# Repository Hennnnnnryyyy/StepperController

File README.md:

# StepperController
A simple handheld stepper controller

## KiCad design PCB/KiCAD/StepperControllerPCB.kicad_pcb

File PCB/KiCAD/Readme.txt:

Attempting to migrate everything to KiCad

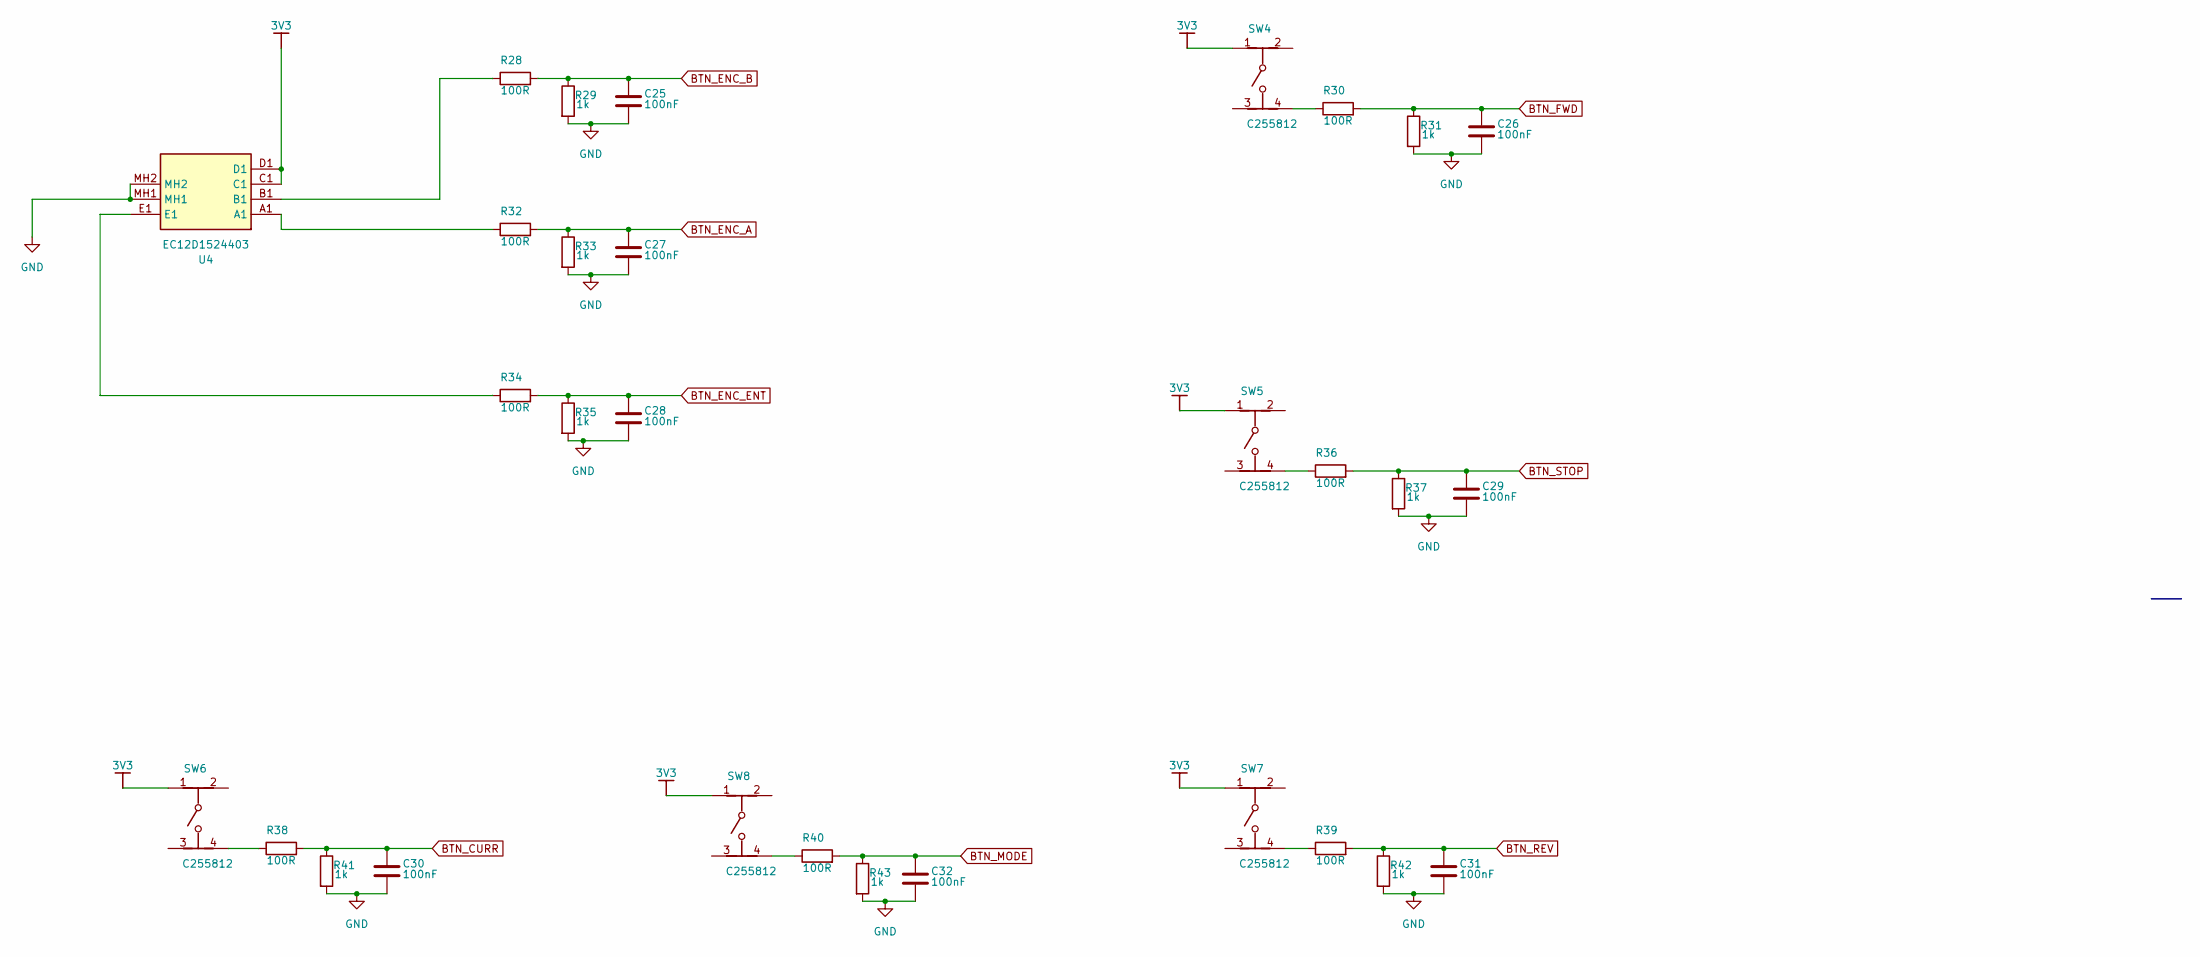
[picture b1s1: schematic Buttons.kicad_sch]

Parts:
C25, C26, C27, C28, C29, C30, C31, C32: 100nF; C_0603_1608Metric
R28, R30, R32, R34, R36, R38, R39, R40: 100R; R_0603_1608Metric
R29, R31, R33, R35, R37, R41, R42, R43: 1k; R_0603_1608Metric
SW4, SW5, SW6, SW7, SW8: C255812; FSM2J_1; VOLTAGE RATING DC 24V; MANUFACTURER PART NUMBER FSM2JSMAA; MOUSER DESCRIPTION Tactile Switches TACTILE 260G FORCE S
U4: EC12D1524403; Mouser Part Number 688-EC12D1524403

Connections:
3V3: SW4.1, SW5.1, SW6.1, SW7.1, SW8.1, U4.C1, U4.D1; also elsewhere on the board
BTN_CURR: C30.1, R38.2, R41.1; also elsewhere on the board
BTN_ENC_A: C27.1, R32.2, R33.1; also elsewhere on the board
BTN_ENC_B: C25.1, R28.2, R29.1; also elsewhere on the board
BTN_ENC_ENT: C28.1, R34.2, R35.1; also elsewhere on the board
BTN_FWD: C26.1, R30.2, R31.1; also elsewhere on the board
BTN_MODE: C32.1, R40.2, R43.1; also elsewhere on the board
BTN_REV: C31.1, R39.2, R42.1; also elsewhere on the board
BTN_STOP: C29.1, R36.2, R37.1; also elsewhere on the board
GND: C25.2, C26.2, C27.2, C28.2, C29.2, C30.2, C31.2, C32.2, R29.2, R31.2, R33.2, R35.2, R37.2, R41.2, R42.2, R43.2, U4.MH1, U4.MH2; also elsewhere on the board
unnamed: R28.1, U4.B1
unnamed: R30.1, SW4.4
unnamed: R32.1, U4.A1
unnamed: R34.1, U4.E1
unnamed: R36.1, SW5.4
unnamed: R38.1, SW6.4
unnamed: R39.1, SW7.4
unnamed: R40.1, SW8.4

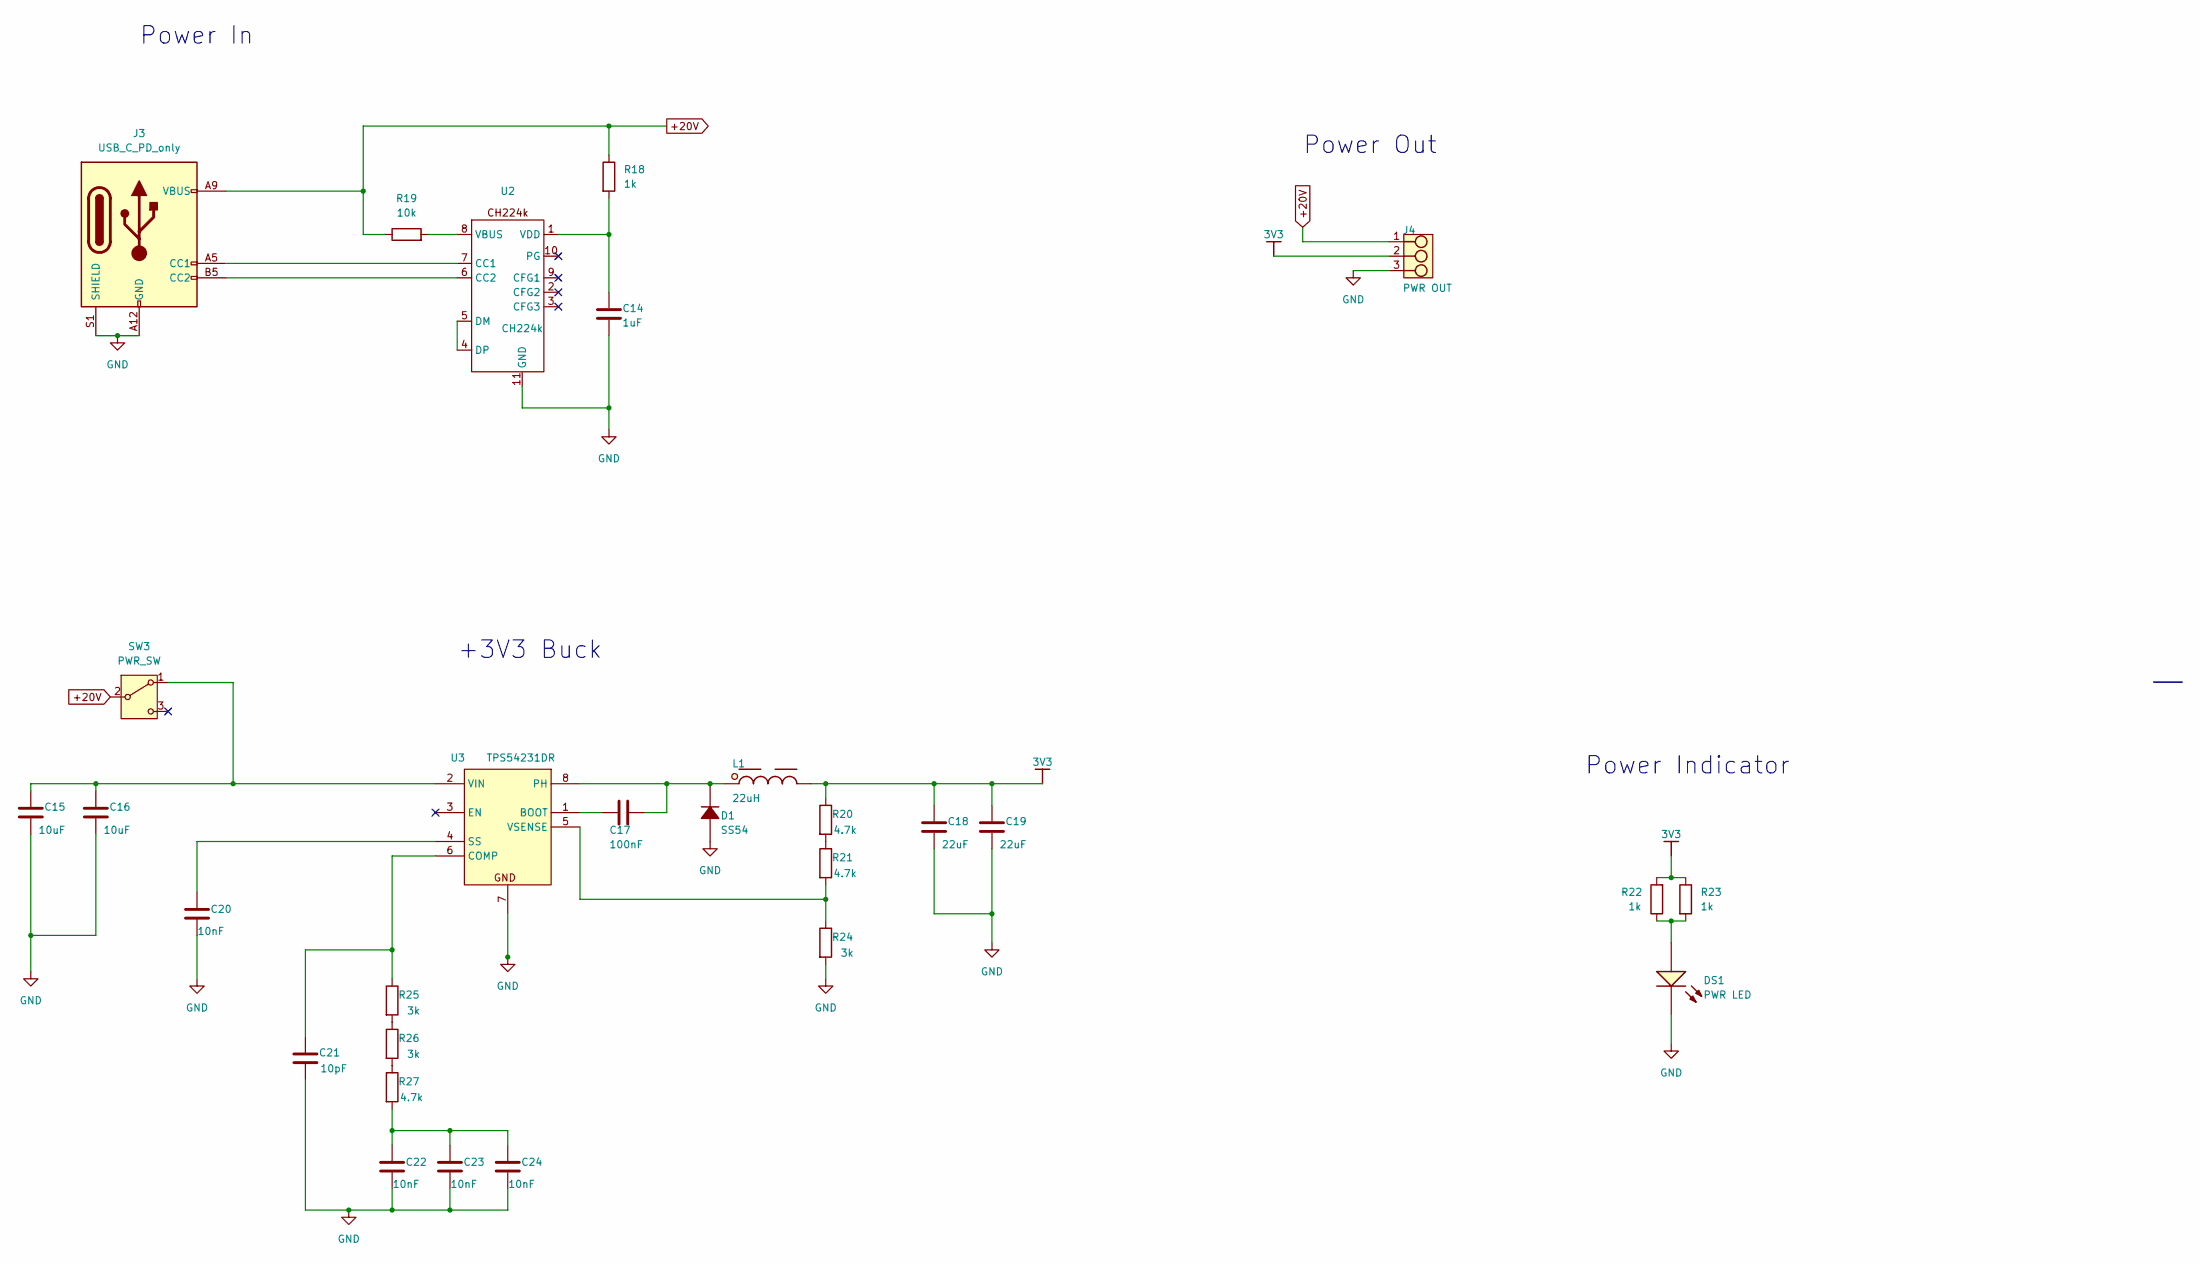
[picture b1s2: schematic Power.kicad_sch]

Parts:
C14: 1uF; C_0603_1608Metric; TOLERANCE ±20%; VOLTAGE - RATED 25V; PART NUMBER 250X14W223MV4T
C15, C16: 10uF; C_1206_3216Metric
C17: 100nF; C_0603_1608Metric
C18, C19: 22uF; C_1206_3216Metric
C20, C22, C23, C24: 10nF; C_0603_1608Metric
C21: 10pF; C_0603_1608Metric
D1: SS54; D_SMA; VOLTAGE - DC REVERSE (V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 50V; VOLTAGE - FORWARD (VF) 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 1.3V @ 1A; PART NUMBER SS54; LCSC C22452
DS1: PWR LED; LED_1206_3216Metric; FORWARD VOLTAGE 1.8V; LCSC C84270
J3: USB_C_PD_only; USB_C_Receptacle_GCT_USB4125-xx-x_6P_TopMnt_Horizontal; LCSC C18357551
J4: PWR OUT; TerminalBlock_RND_205-00288_1x03_P5.08mm_Horizontal; PARTNUMBER 1760500000; LCSC C430602
L1: 22uH; SMDRH105R; INDUCTANCE TOLERANCE 20%; TOLERANCE 20%; LCSC C10165
R18, R22, R23: 1k; R_0603_1608Metric
R19: 10k; R_0603_1608Metric
R20, R21, R27: 4.7k; R_0603_1608Metric
R24, R25, R26: 3k; R_0603_1608Metric
SW3: PWR_SW; Swtich SS-12F44-G5; LCSC C136718
U2: CH224k; SSOP-10_3.9x4.9mm_P1.00mm; LCSC C970725
U3: TPS54231DR; SOIC-8_3.9x4.9mm_P1.27mm; RATING Catalog; PARTNUMBER TPS54231DR; LCSC C28023

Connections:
3V3: C18.1, C19.1, J4.2 (A2), L1.2, R20.1, R22.2, R23.1; also elsewhere on the board
+20V: J3.A9 (VBUS), J3.B9 (VBUS), J4.1 (A1), R18.1, R19.1, SW3.2 (B); also elsewhere on the board
GND: C14.2, C15.2, C16.2, C18.2, C19.2, C20.2, C21.2, C22.2, C23.2, C24.2, D1.1, DS1.2 (K), J3.A12 (GND), J3.B12 (GND), J3.S1 (SHIELD), J4.3 (A3), R24.2, U2.11 (GND), U3.7 (GND); also elsewhere on the board
unnamed: C22.1, C23.1, C24.1, R27.2
unnamed: DS1.1 (A), R22.1, R23.2
unnamed: J3.A5 (CC1), U2.7 (CC1)
unnamed: J3.B5 (CC2), U2.6 (CC2)
unnamed: R20.2, R21.1
unnamed: R25.2, R26.1
unnamed: R26.2, R27.1
unnamed: C15.1, C16.1, SW3.1 (A), U3.2 (VIN)
unnamed: U2.4 (DP), U2.5 (DM)
unnamed: R19.2, U2.8 (VBUS)
unnamed: C14.1, R18.2, U2.1 (VDD)
unnamed: C17.2, U3.1 (BOOT)
unnamed: C21.1, R25.1, U3.6 (COMP)
unnamed: C17.1, D1.2, L1.1, U3.8 (PH)
unnamed: C20.1, U3.4 (SS)
unnamed: R21.2, R24.1, U3.5 (VSENSE)

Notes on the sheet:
Power Out
Power In
+3V3 Buck
Power Indicator

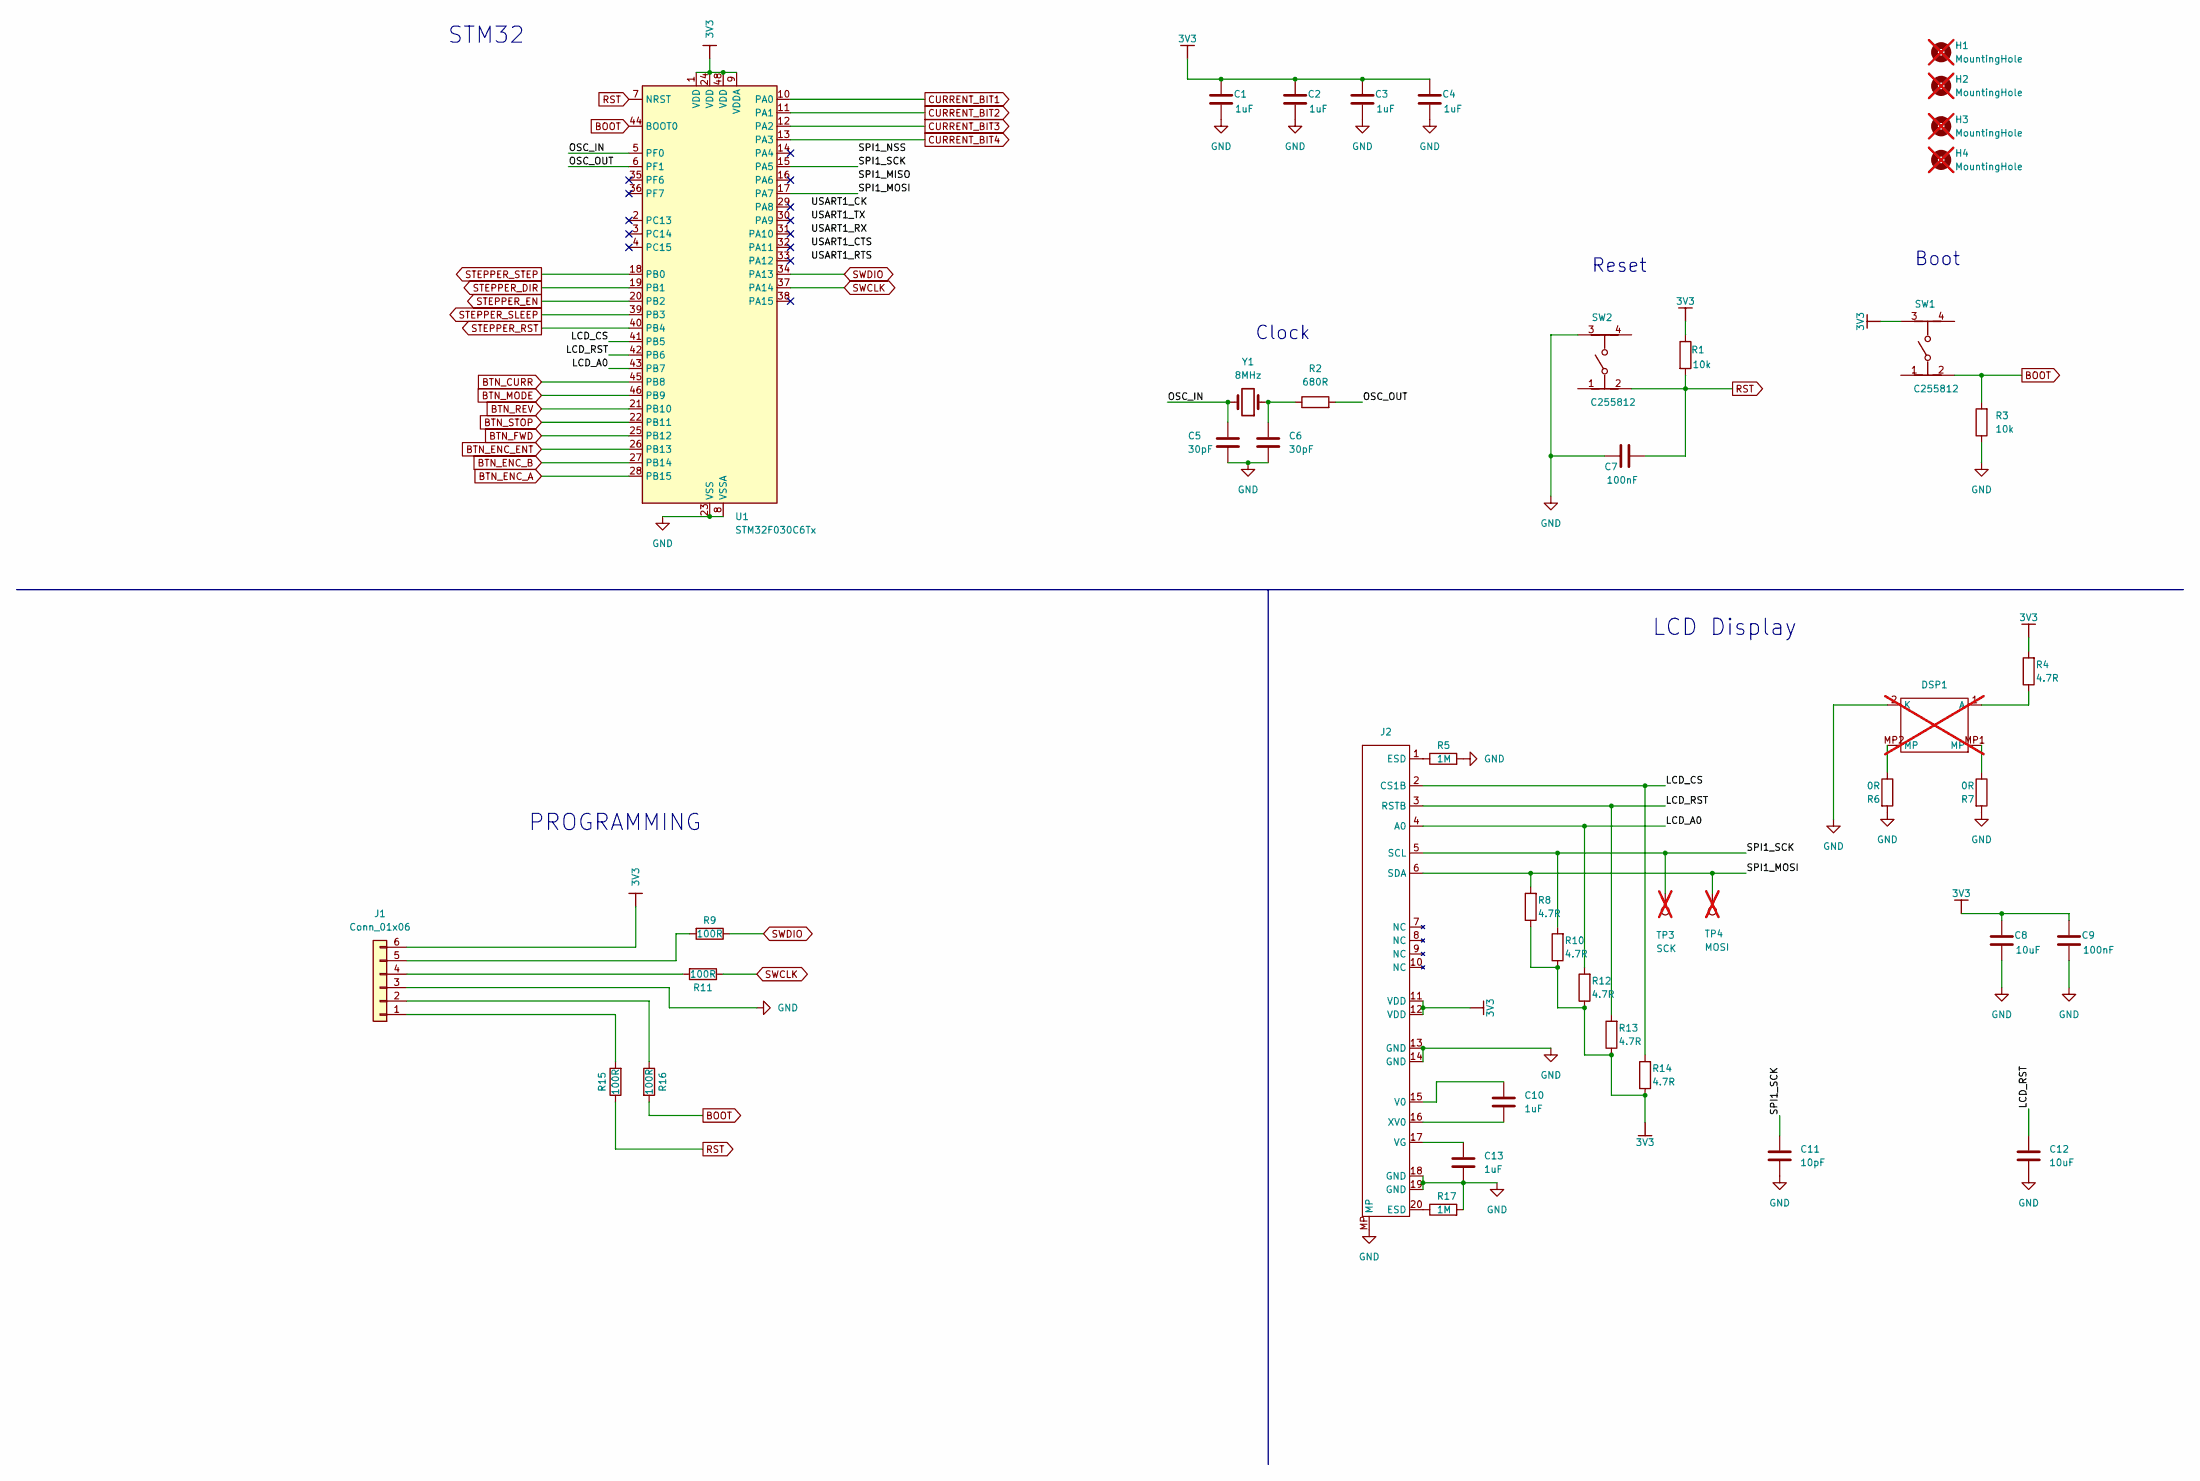
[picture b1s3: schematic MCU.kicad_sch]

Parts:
C1, C2, C3, C4, C10, C13: 1uF; C_0603_1608Metric
C5, C6: 30pF; C_0603_1608Metric
C7, C9: 100nF; C_0603_1608Metric
C8, C12: 10uF; C_1206_3216Metric
C11: 10pF; C_0603_1608Metric
DSP1: HS12864G19C Display; not fitted
H1, H2, H3, H4: MountingHole; MountingHole_3.2mm_M3; not fitted
J1: Conn_01x06; PinHeader_1x06_P2.54mm_Vertical; LCSC C37208
J2: AFC01-S20FFC-00; LCSC C262274
R1, R3: 10k; R_0603_1608Metric
R2: 680R; R_0603_1608Metric
R4, R8, R10, R12, R13, R14: 4.7R; R_0603_1608Metric
R5, R17: 1M; R_0603_1608Metric
R6, R7: 0R; R_0603_1608Metric
R9, R11, R15, R16: 100R; R_0603_1608Metric
SW1, SW2: C255812; FSM2J_1; VOLTAGE RATING DC 24V; MANUFACTURER PART NUMBER FSM2JSMAA; MOUSER DESCRIPTION Tactile Switches TACTILE 260G FORCE S
TP3: SCK; TestPoint_Pad_D2.0mm; not fitted
TP4: MOSI; TestPoint_Pad_D2.0mm; not fitted
U1: STM32F030C6Tx; LQFP-48_7x7mm_P0.5mm; LCSC C62514
Y1: 8MHz; Crystal_SMD_HC49-SD; LCSC C12674

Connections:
3V3: C1.1, C2.1, C3.1, C4.1, C8.1, C9.1, J1.6, J2.11 (VDD), J2.12 (VDD), R1.1, R4.2, R8.1, R10.1, R12.1, R13.1, R14.1, SW1.3, U1.1 (VDD), U1.9 (VDDA), U1.24 (VDD), U1.48 (VDD); also elsewhere on the board
/MCU/LCD_A0: J2.4 (A0), R12.2, U1.43 (PB7)
/MCU/LCD_CS: J2.2 (CS1B), R14.2, U1.41 (PB5)
/MCU/LCD_RST: C12.1, J2.3 (RSTB), R13.2, U1.42 (PB6)
/MCU/OSC_IN: C5.2, U1.5 (PF0), Y1.2
/MCU/OSC_OUT: R2.2, U1.6 (PF1)
/MCU/SPI1_MOSI: J2.6 (SDA), R8.2, TP4.1, U1.17 (PA7)
/MCU/SPI1_SCK: C11.1, J2.5 (SCL), R10.2, TP3.1, U1.15 (PA5)
BOOT: R3.2, R16.2, SW1.2, U1.44 (BOOT0)
BTN_CURR: U1.45 (PB8); also elsewhere on the board
BTN_ENC_A: U1.28 (PB15); also elsewhere on the board
BTN_ENC_B: U1.27 (PB14); also elsewhere on the board
BTN_ENC_ENT: U1.26 (PB13); also elsewhere on the board
BTN_FWD: U1.25 (PB12); also elsewhere on the board
BTN_MODE: U1.46 (PB9); also elsewhere on the board
BTN_REV: U1.21 (PB10); also elsewhere on the board
BTN_STOP: U1.22 (PB11); also elsewhere on the board
CURRENT_BIT1: U1.10 (PA0); also elsewhere on the board
CURRENT_BIT2: U1.11 (PA1); also elsewhere on the board
CURRENT_BIT3: U1.12 (PA2); also elsewhere on the board
CURRENT_BIT4: U1.13 (PA3); also elsewhere on the board
GND: C1.2, C2.2, C3.2, C4.2, C5.1, C6.1, C7.1, C8.2, C9.2, C11.2, C12.2, C13.2, DSP1.2 (K), J1.3, J2.13 (GND), J2.14 (GND), J2.18 (GND), J2.19 (GND), J2.MP, R3.1, R5.2, R6.2, R7.2, R17.2, SW2.3, U1.8 (VSSA), U1.23 (VSS), U1.47 (VSS); also elsewhere on the board
unnamed: C6.2, R2.1, Y1.1
unnamed: DSP1.1 (A), R4.1
unnamed: DSP1.MP1 (MP), R7.1
unnamed: DSP1.MP2 (MP), R6.1
unnamed: J1.1, R15.2
unnamed: J1.2, R16.1
unnamed: J1.4, R11.2
unnamed: J1.5, R9.2
unnamed: J2.1 (ESD), R5.1
unnamed: J2.20 (ESD), R17.1
unnamed: C10.1, J2.15 (V0)
unnamed: C13.1, J2.17 (VG)
unnamed: C10.2, J2.16 (XV0)
RST: C7.2, R1.2, R15.1, SW2.2, U1.7 (NRST)
STEPPER_DIR: U1.19 (PB1); also elsewhere on the board
STEPPER_EN: U1.20 (PB2); also elsewhere on the board
STEPPER_RST: U1.40 (PB4); also elsewhere on the board
STEPPER_SLEEP: U1.39 (PB3); also elsewhere on the board
STEPPER_STEP: U1.18 (PB0); also elsewhere on the board
SWCLK: R11.1, U1.37 (PA14)
SWDIO: R9.1, U1.34 (PA13)

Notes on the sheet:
Reset
Clock
Boot
LCD Display
STM32
PROGRAMMING

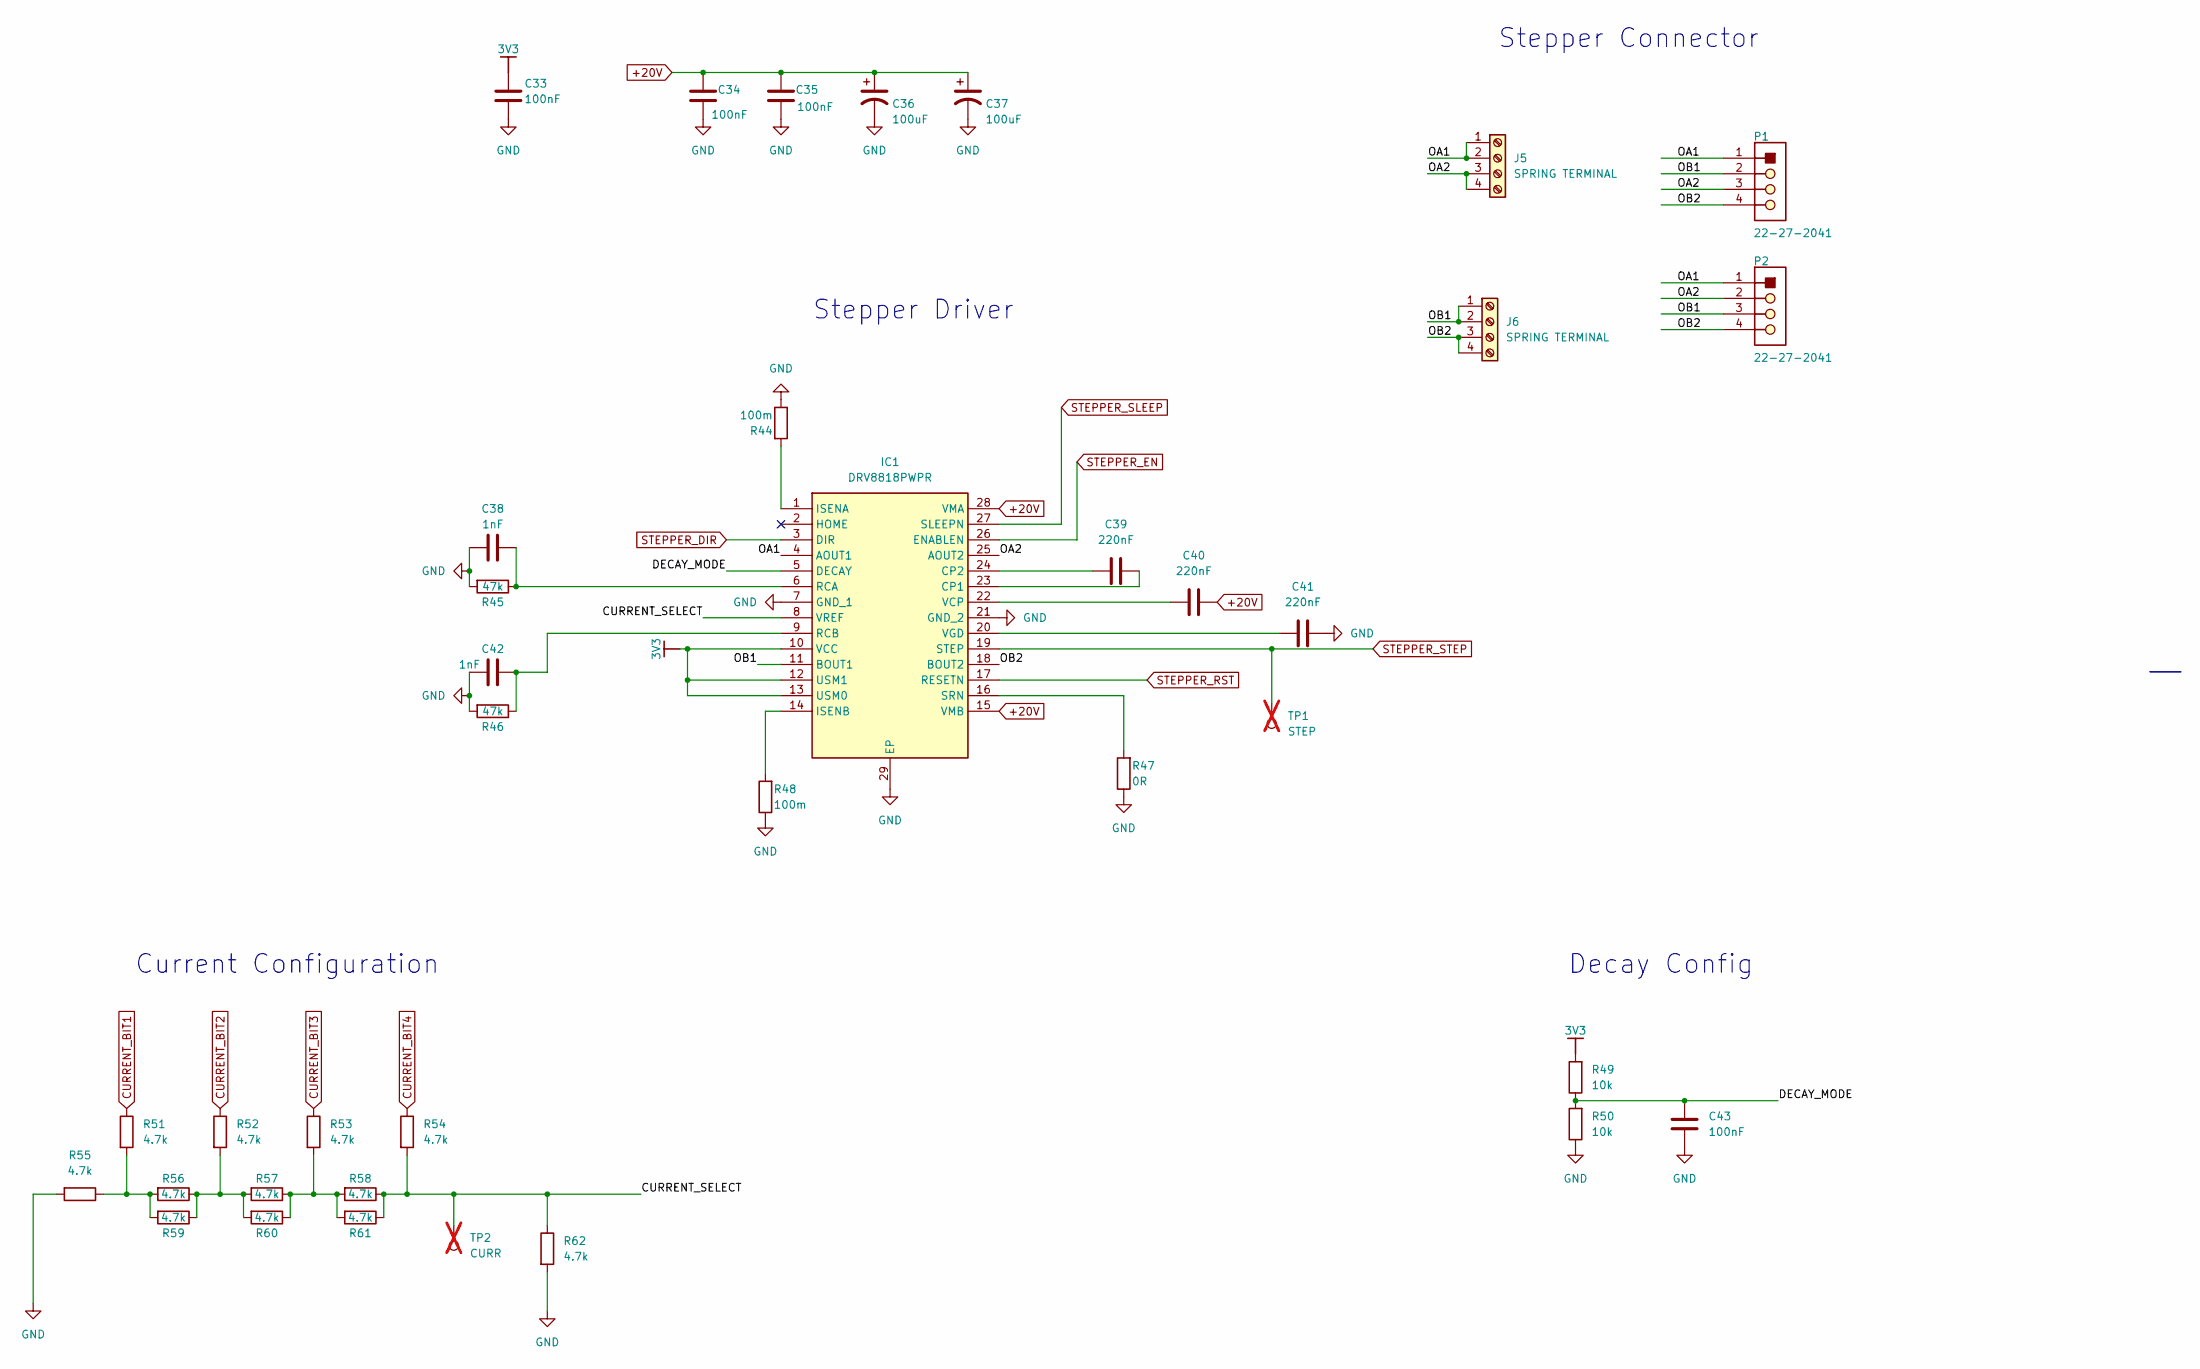
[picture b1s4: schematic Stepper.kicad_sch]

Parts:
C33, C34, C35, C43: 100nF; C_0603_1608Metric
C36, C37: 100uF; CP_Elec_8x10; LCSC C176665
C38, C42: 1nF; C_0603_1608Metric
C39, C40, C41: 220nF; C_0603_1608Metric
IC1: DRV8818PWPR; SOP65P640X120-29N; Mouser Part Number 595-DRV8818PWPR
J5, J6: SPRING TERMINAL; MX235-5.0-04P; LCSC C5349564
P1, P2: 22-27-2041; Molex_KK-254_AE-6410-04A_1x04_P2.54mm_Vertical; VOLTAGE RATING 250V; CURRENT RATING 4A; LCSC C239364
R44, R48: 100m; R_1206_3216Metric
R45, R46: 47k; R_0603_1608Metric
R47: 0R; R_0603_1608Metric
R49, R50: 10k; R_0603_1608Metric
R51, R52, R53, R54, R55, R56, R57, R58, R59, R60, R61, R62: 4.7k; R_0603_1608Metric
TP1: STEP; TestPoint_Pad_D2.0mm; not fitted
TP2: CURR; TestPoint_Pad_D2.0mm; not fitted

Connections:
3V3: C33.1, IC1.10 (VCC), IC1.12 (USM1), IC1.13 (USM0), R49.2; also elsewhere on the board
+20V: C34.1, C35.1, C36.1, C37.1, C40.2, IC1.15 (VMB), IC1.28 (VMA); also elsewhere on the board
/Stepper/CURRENT_SELECT: IC1.8 (VREF), R54.2, R58.1, R61.1, R62.1, TP2.1
/Stepper/DECAY_MODE: C43.1, IC1.5 (DECAY), R49.1, R50.2
/Stepper/OA1: IC1.4 (AOUT1), J5.1, J5.2, P1.1, P2.1
/Stepper/OA2: IC1.25 (AOUT2), J5.3, J5.4, P1.3, P2.2
/Stepper/OB1: IC1.11 (BOUT1), J6.1, J6.2, P1.2, P2.3
/Stepper/OB2: IC1.18 (BOUT2), J6.3, J6.4, P1.4, P2.4
CURRENT_BIT1: R51.1; also elsewhere on the board
CURRENT_BIT2: R52.1; also elsewhere on the board
CURRENT_BIT3: R53.1; also elsewhere on the board
CURRENT_BIT4: R54.1; also elsewhere on the board
GND: C33.2, C34.2, C35.2, C36.2, C37.2, C38.1, C41.2, C42.1, C43.2, IC1.7 (GND_1), IC1.21 (GND_2), IC1.29 (EP), R44.1, R45.2, R46.2, R47.1, R48.1, R50.1, R55.2, R62.2; also elsewhere on the board
unnamed: C39.2, IC1.23 (CP1)
unnamed: C39.1, IC1.24 (CP2)
unnamed: IC1.1 (ISENA), R44.2
unnamed: IC1.14 (ISENB), R48.2
unnamed: C38.2, IC1.6 (RCA), R45.1
unnamed: C42.2, IC1.9 (RCB), R46.1
unnamed: IC1.16 (SRN), R47.2
unnamed: C40.1, IC1.22 (VCP)
unnamed: C41.1, IC1.20 (VGD)
unnamed: R51.2, R55.1, R56.2, R59.2
unnamed: R52.2, R56.1, R57.2, R59.1, R60.2
unnamed: R53.2, R57.1, R58.2, R60.1, R61.2
STEPPER_DIR: IC1.3 (DIR); also elsewhere on the board
STEPPER_EN: IC1.26 (ENABLEN); also elsewhere on the board
STEPPER_RST: IC1.17 (RESETN); also elsewhere on the board
STEPPER_SLEEP: IC1.27 (SLEEPN); also elsewhere on the board
STEPPER_STEP: IC1.19 (STEP), TP1.1; also elsewhere on the board

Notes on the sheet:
Current Configuration
Stepper Connector
Stepper Driver
Decay Config

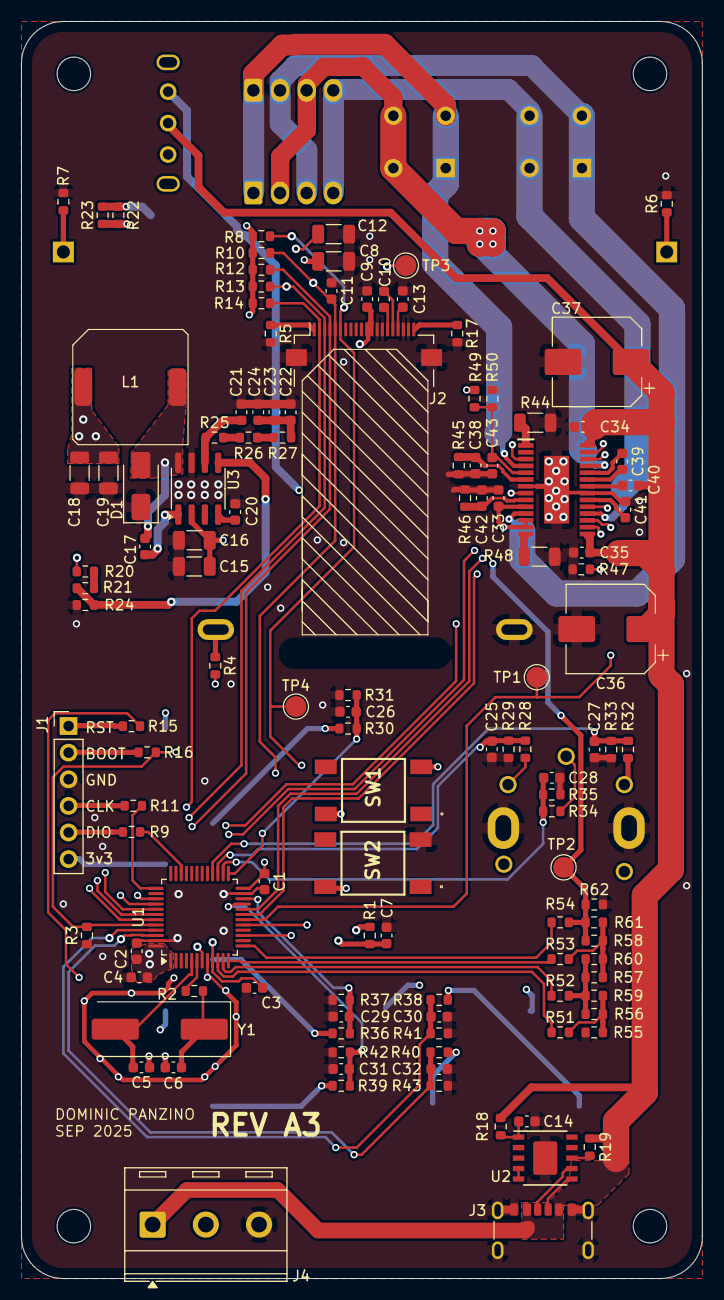
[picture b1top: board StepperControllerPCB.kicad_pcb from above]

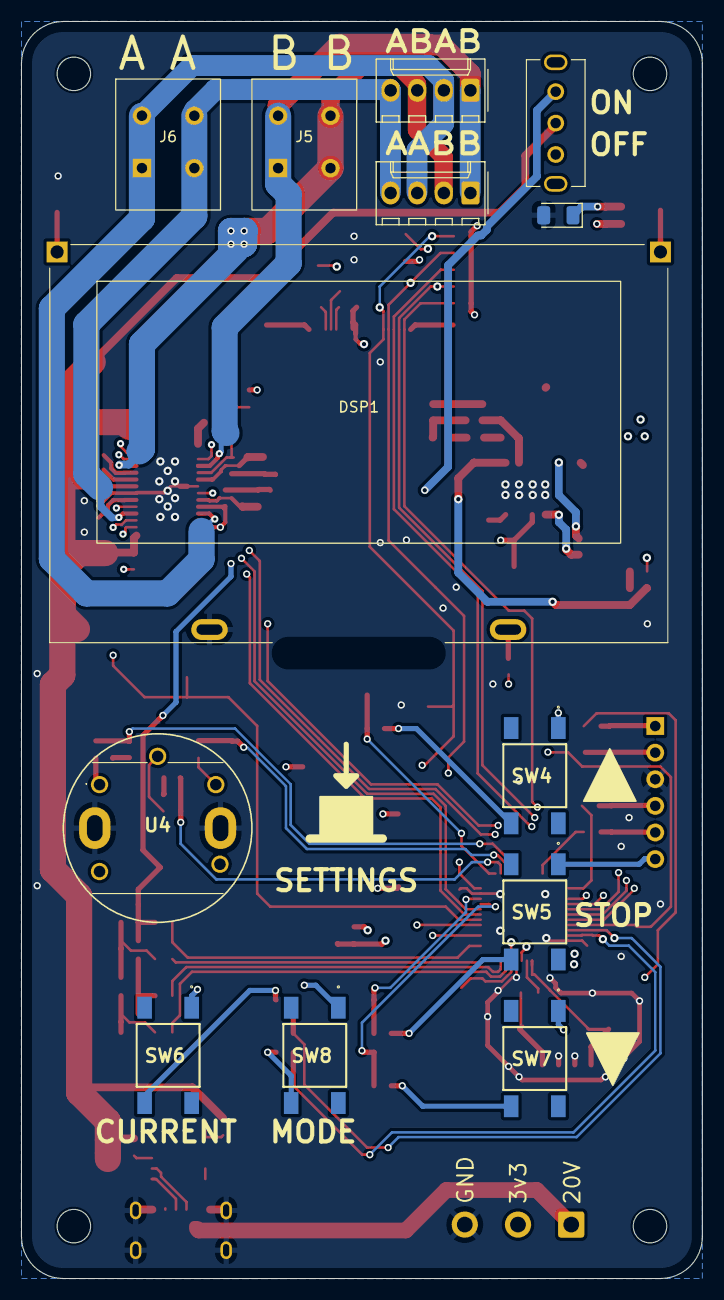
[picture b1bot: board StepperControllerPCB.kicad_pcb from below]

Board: 4 copper layers, 65.0 x 120.0 mm, 139 parts (13 on the bottom side), 86 nets.

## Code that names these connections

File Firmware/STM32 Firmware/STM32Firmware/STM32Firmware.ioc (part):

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Mcu.Name=STM32F030C6Tx
Mcu.Package=LQFP48
Mcu.UserName=STM32F030C6Tx
PA0.GPIOParameters=GPIO_Label
PA0.GPIO_Label=CurrentBit1
PA0.Signal=GPIO_Output
PA1.GPIOParameters=GPIO_Label
PA1.GPIO_Label=CurrentBit2
PA1.Signal=GPIO_Output
PA13.Mode=Serial_Wire
PA13.Signal=SYS_SWDIO
PA14.Mode=Serial_Wire
PA14.Signal=SYS_SWCLK
PA2.GPIOParameters=GPIO_Label
PA2.GPIO_Label=CurrentBit3
PA2.Signal=GPIO_Output
PA3.GPIOParameters=GPIO_Label
PA3.GPIO_Label=CurrentBit4
PA3.Signal=GPIO_Output
PA4.Signal=SPI1_NSS
PA5.Mode=TX_Only_Simplex_Unidirect_Master
PA5.Signal=SPI1_SCK
PA6.Signal=SPI1_MISO
PA7.Mode=TX_Only_Simplex_Unidirect_Master
PA7.Signal=SPI1_MOSI
PB0.GPIOParameters=GPIO_Label
PB0.GPIO_Label=StepperStep
PB0.Signal=GPIO_Output
PB1.GPIOParameters=GPIO_Label
PB1.GPIO_Label=StepperDir
PB1.Signal=GPIO_Output
PB10.GPIOParameters=GPIO_Label
PB10.GPIO_Label=RevBtn
PB10.Signal=GPIO_Input
PB11.GPIOParameters=GPIO_Label
PB11.GPIO_Label=StopBtn
PB11.Signal=GPIO_Input
PB12.GPIOParameters=GPIO_Label
PB12.GPIO_Label=FwdBtn
PB12.Signal=GPIO_Input
PB13.GPIOParameters=GPIO_Label
PB13.GPIO_Label=EncBtn
PB13.Signal=GPIO_Input
PB14.GPIOParameters=GPIO_Label
PB14.GPIO_Label=EncB
PB14.Signal=GPIO_Input
PB15.GPIOParameters=GPIO_ModeDefaultEXTI
PB15.GPIO_ModeDefaultEXTI=GPIO_MODE_IT_RISING_FALLING
PB15.Signal=GPXTI15
PB2.GPIOParameters=GPIO_Label
PB2.GPIO_Label=StepperEn
PB2.Signal=GPIO_Output
PB3.GPIOParameters=GPIO_Label
PB3.GPIO_Label=StepperSleep
PB3.Signal=GPIO_Output
PB4.GPIOParameters=GPIO_Label
PB4.GPIO_Label=StepperRst
PB4.Signal=GPIO_Output
PB5.GPIOParameters=GPIO_Label
PB5.GPIO_Label=LCDcs
PB5.Signal=GPIO_Output
PB6.GPIOParameters=GPIO_Label
PB6.GPIO_Label=LCDrst
PB6.Signal=GPIO_Output
PB7.GPIOParameters=GPIO_Label
PB7.GPIO_Label=LCDa0
PB7.Signal=GPIO_Output
PB8.GPIOParameters=GPIO_Label
PB8.GPIO_Label=CurrBtn
PB8.Signal=GPIO_Input
PB9.GPIOParameters=GPIO_Label
PB9.GPIO_Label=ModeBtn
PB9.Signal=GPIO_Input
PF0-OSC_IN.Mode=HSE-External-Oscillator
PF0-OSC_IN.Signal=RCC_OSC_IN
PF1-OSC_OUT.Mode=HSE-External-Oscillator
PF1-OSC_OUT.Signal=RCC_OSC_OUT
RCC.SYSCLKFreq_VALUE=32000000
RCC.SYSCLKSource=RCC_SYSCLKSOURCE_PLLCLK
board=custom

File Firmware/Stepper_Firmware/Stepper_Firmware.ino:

#include <SPI.h>
#include <Adafruit_GFX.h>
#include <Adafruit_SSD1305.h>
#include <Preferences.h>
#include <AccelStepper.h>
#include <esp_task_wdt.h>
#include <TMCStepper.h>

// -------------------------------- Pin Definition --------------------------------
#define STEP_PIN 15
#define DIR_PIN 16
#define EN_PIN 17
#define STEP_UART_PIN 18
#define STEP_DIAG_PIN 19

#define SCLK_PIN 6
#define MOSI_PIN 4
#define OLED_CS_PIN 8
#define OLED_DC_PIN 10
#define OLED_RESET_PIN 9

#define BTN_FWD_PIN 38
#define BTN_STOP_PIN 39
#define BTN_REV_PIN 40
#define BTN_MODE_PIN 42       // I fucked up the schematic, these are flipped
#define BTN_CURRENT_PIN 41  // I fucked up the schematic, these are flipped

#define ENC_A_PIN 35
#define ENC_B_PIN 36
#define ENC_BTN_PIN 37

#define STEPS_PER_REV 1600
#define ENCODER_POS_TO_REV 0.05

// -------------------------------- Variables --------------------------------
// floats give me the ick
float stepper_setSpeed = 1;
float stepper_setAccel = 10;
float stepper_setPos = 0;
float stepper_setMulti = 1;
float stepper_setDist = 1;

int stepper_mode = 0;  // 0 = momentary, 1 = continous, 2 = manJog, 3 = Reciprocate
int stepper_current = 1000;
int cycleCount = 0;

// Encoder wheel stuff
int encoderMode = 0;  // Current mode
struct EncoderParametersStruct {
  float* variable;       // Pointer to the variable we want to modify
  float minVal;          // Minimum value for the variable
  float maxVal;          // Maximum value for the variable
  float fineStepSize;    // Step size for each increment/decrement
  float midStepSize;     // Step size for each increment/decrement
  float coarseStepSize;  // Step size for each increment/decrement
};
EncoderParametersStruct encoderParameter[] = {
  // variable, minVal, maxVal, fine, mid, coarse step size
  { &stepper_setSpeed, 0.01, 25, 0.01, 0.1, 1 },
  { &stepper_setAccel, 0.01, 9999.9, 0.1, 1, 10 },
  { &stepper_setPos, -9999999, 9999999, 1, 1, 1 },
  { &stepper_setMulti, 0.01, 999.99, 0.01, 0.1, 1 },
  { &stepper_setDist, 0.01, 999.99, 0.01, 0.1, 1 },
};

// -------------------------------- Classes --------------------------------
// Edge detector
class edgeDetector {  // Returns 1 on rising edge. How there is no built in function for detecting rising edge that's not ISR baffles me...
public:
  edgeDetector(int pin)
    : pin(pin), lastState(0) {
    pinMode(pin, INPUT);
  }
  bool risingEdge() {
    int currentState = digitalRead(pin);
    bool isRisingEdge = (lastState == 0 && currentState == 1);
    lastState = currentState;
    return isRisingEdge;
  }

private:
  int pin;
  int lastState;
};

edgeDetector btn_fwd(BTN_FWD_PIN);
edgeDetector btn_stop(BTN_STOP_PIN);
edgeDetector btn_rev(BTN_REV_PIN);
edgeDetector btn_mode(BTN_MODE_PIN);
edgeDetector btn_current(BTN_CURRENT_PIN);
edgeDetector btn_enc(ENC_BTN_PIN);


// Stepper Driver
class TMCstepperDriver {  // Configures TMC stepper driver
private:
  TMC2209Stepper drv;
public:
  TMCstepperDriver()
    : drv(&Serial2, 0.1f, 0b00) {  // Serial port, sense resistor, driver address
  }
  void begin();                  // Initialize stepper driver
  void setMode(bool mode);       // Set driver to 1 = StealthChop (for homing) or 0 = SpreadCycle (for printing) mode
  void setCurrent(int current);  // Set motor current
  void disable(bool disable);    // 1 to disable motor coils
};

TMCstepperDriver stepperDriver;  // Stepper Driver

// Rest of the stuff
SPIClass myFSPI(FSPI);  // SPI bus for OLED
Adafruit_SSD1305 display(128, 64, &myFSPI, OLED_DC_PIN, OLED_RESET_PIN, OLED_CS_PIN);  // OLED Display
AccelStepper stepper(1, STEP_PIN, DIR_PIN);
// -------------------------------- Main --------------------------------
void setup() {
  Serial.begin(115200);
  pinMode(STEP_PIN, OUTPUT);
  pinMode(DIR_PIN, OUTPUT);
  pinMode(EN_PIN, OUTPUT);
  pinMode(STEP_UART_PIN, OUTPUT);
  pinMode(STEP_DIAG_PIN, INPUT);

  pinMode(SCLK_PIN, OUTPUT);
  pinMode(MOSI_PIN, OUTPUT);
  pinMode(OLED_CS_PIN, OUTPUT);
  pinMode(OLED_DC_PIN, OUTPUT);
  pinMode(OLED_RESET_PIN, OUTPUT);

  pinMode(BTN_FWD_PIN, INPUT);
  pinMode(BTN_STOP_PIN, INPUT);
  pinMode(BTN_REV_PIN, INPUT);
  pinMode(BTN_MODE_PIN, INPUT);
  pinMode(BTN_CURRENT_PIN, INPUT);

  pinMode(ENC_A_PIN, INPUT_PULLDOWN);
  pinMode(ENC_B_PIN, INPUT_PULLDOWN);
  pinMode(ENC_BTN_PIN, INPUT);

  myFSPI.begin(SCLK_PIN, -1, MOSI_PIN, -1);
  stepperDriver.begin();

  stepper.setMaxSpeed(99999999);
  stepper.setAcceleration(99999999);

  xTaskCreatePinnedToCore(DisplayTask, "DisplayTask", 50000, NULL, 0, NULL, 0);
  xTaskCreatePinnedToCore(EncoderTask, "EncoderTask", 5000, NULL, 1, NULL, 0);

  xTaskCreatePinnedToCore(StepperTask, "StepperTask", 5000, NULL, 100, NULL, 1);
}

void loop() {
  vTaskDelay(1000 / portTICK_PERIOD_MS);
}

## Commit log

2025-08-11 correcting some comments
2025-08-11 Creat KiCad folder
2025-08-11 Adding initial KiCAD files.
2025-08-13 Conslidated the firmware
2025-08-20 Initial PCB draft
2025-09-03 New PCB design
2025-09-03 Added name silkscreen
2025-09-20 purchased board
2025-11-26 STM32 Firmware
